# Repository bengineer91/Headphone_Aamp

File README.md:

Opamp based headphone amplifier. 

**Digital Side**

Momentary push button feeds a schmitt trigger and D flip flop to turn the board on and off. A USB-C connector with 5.1k resistors on the CC pins sets it up for 5V 3A max - this is mainly because I couldn't find a sufficiently simple USB-C PD Sink IC that I liked. Even the simple ones seemed overly complex so my conclusion is I'm not the target audience of where the industry is headed.

**Analog Side**

Isolated DC/DC converter takes 5V in and spits out +/-12V. This then feeds through an LDO to regulate the split rails at roughly +/-10V. Audio path is a 10k potentiometer, OPA1656 provides high and low pass filtering along with gain, then parallel stages of OPA1678 provide the output stage.

Sound quality is excellent although I already have a list of issues and improvements for next time. [Fixed] indicates the files uploaded here have this incorporated. I don't have a scope to make any measurements - only thing I checked was voltage rails and DC offset with my multimeter.

1. [Fixed] Connect LDO enable to VIN. (I had to make a daughterboard on the revision I built).
2. Anti-pop circuit on output.
3. [Fixed] Add cap (C35) so the on/off circuit defaults to off at power application.
4. Add switchable dummy load for testing before connecting headphones.
5. Trimpot for LED brightness.
6. Adjustable gain

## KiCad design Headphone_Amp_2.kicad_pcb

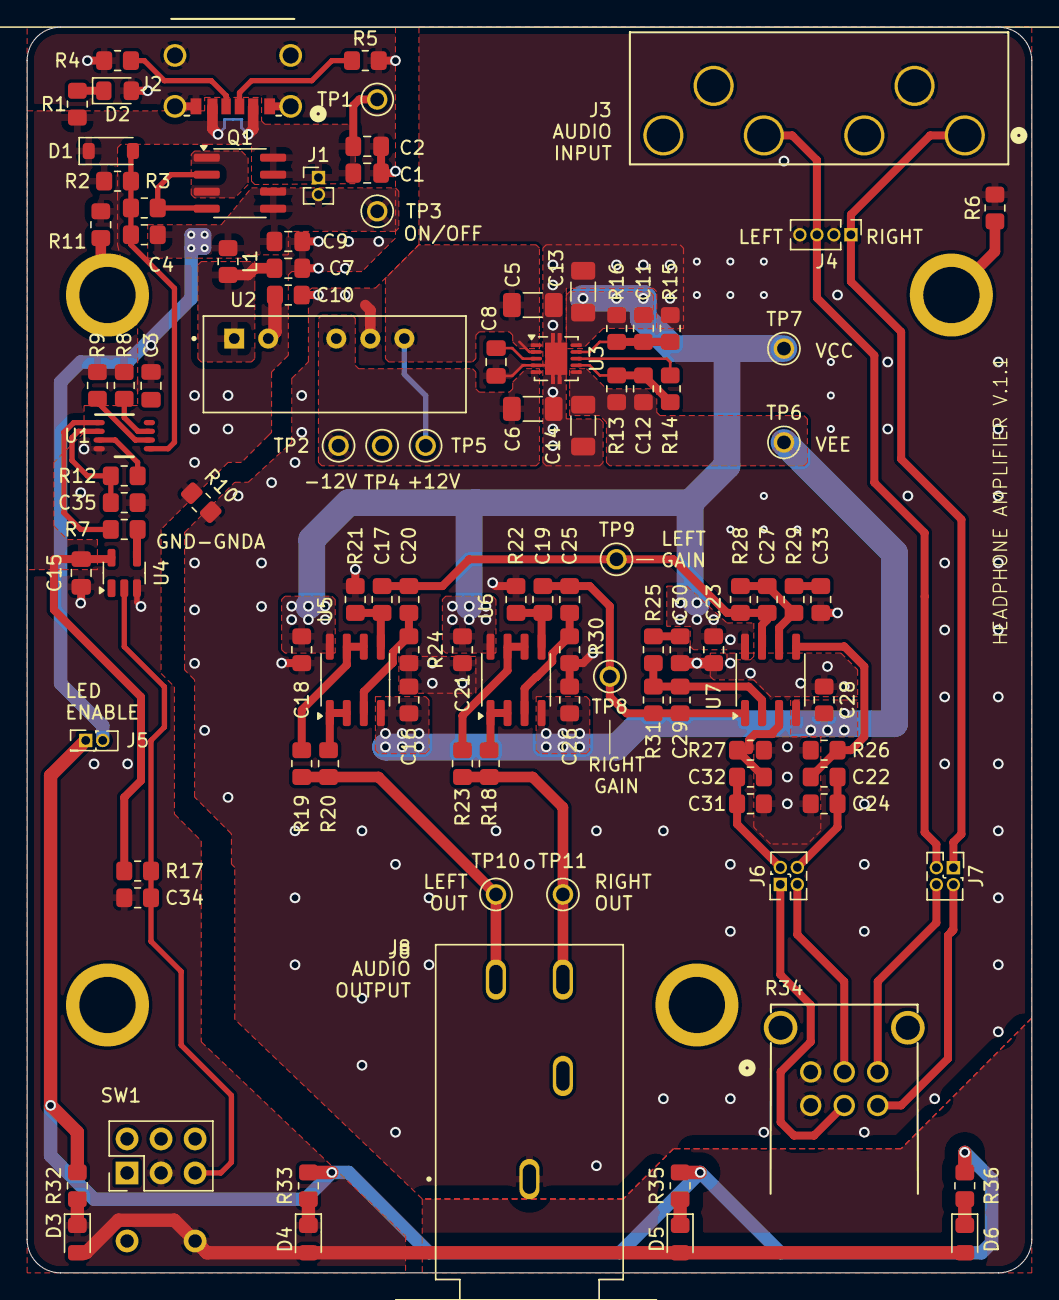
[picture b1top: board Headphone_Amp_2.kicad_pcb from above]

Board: 2 copper layers, 75.0 x 93.0 mm, 111 parts (1 on the bottom side), 59 nets.

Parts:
C1, C8: 0.01u; C_0805_2012Metric_Pad1.18x1.45mm_HandSolder
C2, C7, C9: 4.7u; C_0805_2012Metric_Pad1.18x1.45mm_HandSolder
C3, C15: 0.1u; C_0805_2012Metric_Pad1.18x1.45mm_HandSolder
C4, C34: 1000p; C_0805_2012Metric_HandSolder
C5, C6, C13, C14: 10u; C_1206_3216Metric_Pad1.33x1.80mm_HandSolder
C10: 1n; C_0805_2012Metric_HandSolder
C11, C12: 10n; C_0805_2012Metric_HandSolder
C16, C18, C21, C23, C26, C28: 100n; C_0805_2012Metric_HandSolder
C17, C19, C20, C22, C25, C30, C32, C33: 1u; C_0805_2012Metric_HandSolder
C24, C27, C29, C31: 68p; C_0805_2012Metric_HandSolder
C35: 22p; C_0805_2012Metric_HandSolder
D1: MMSZ5238BT1G; D_SOD-123
D2, D3, D4, D5, D6: LED; LED_0805_2012Metric_Pad1.15x1.40mm_HandSolder
H1, H2, H3, H4: MountingHole; Keystone_M3_Standoff
J1: Conn_02x01; PinHeader_1x02_P1.27mm_Vertical
J2: USB4125-GF-A-0190; CONN6_125-GF-A-0190_GCT
J3: PJRAN2X1U01AUX; CONN6_984x394_SWC_BS
J4: Conn_01x04; PinHeader_1x04_P1.27mm_Vertical
J5: Conn_02x01; PinHeader_2x01_P1.27mm_Vertical
J6, J7: Conn_02x02_Odd_Even; PinHeader_2x02_P1.27mm_Vertical
J8: SJ-63063B; CUI_SJ-63063B
L1: 6.8u; R_0805_2012Metric_HandSolder
Q1: IRF7324; SOIC-8_3.9x4.9mm_P1.27mm
R1, R32, R33, R35, R36: 150; R_0805_2012Metric_HandSolder
R2, R17: 10K; R_0805_2012Metric_HandSolder
R3, R7: 47; R_0805_2012Metric_HandSolder
R4, R5: 5.1K; R_0805_2012Metric_HandSolder
R6, R8, R9, R10, R11: 0; R_0805_2012Metric_HandSolder
R12: 330; R_0805_2012Metric_HandSolder
R13: 84.5k; R_0805_2012Metric_HandSolder
R14, R15, R21, R22, R24, R25, R26, R27, R28, R29, R30, R31: 10k; R_0805_2012Metric_HandSolder
R16: 75k; R_0805_2012Metric_HandSolder
R18, R19, R20, R23: 1; R_0805_2012Metric_HandSolder
R34: RK09L12B0A4S; RK09L12B0A4S_AAL
SW1: BB15AH-FA; BB16AH
TP1, TP2, TP3, TP4, TP5, TP6, TP7, TP8, TP9, TP10, TP11: 5020; KEYSTONE_5020
U1: SN74LVC1G74DCTR; DCT0008A_L
U2: PCN2-S5-D12-S; CONV_PCN2-S5-D12-S
U3: TPS7A39; Texas_S-PVSON-N10
U4: 74LVC1G17; SOT-23-5
U5, U6: OPA1678; SOIC-8_3.9x4.9mm_P1.27mm
U7: OPA1656ID; SOIC-8_3.9x4.9mm_P1.27mm
U8: TVS2200DRV; WSON-6-1EP_2x2mm_P0.65mm_EP1x1.6mm

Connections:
/USBC Input/USBC_CC1: J2.A5 (CC1), R5.1
/USBC Input/USBC_CC2: J2.B5 (CC2), R4.1
GND: C1.2, C2.2, C3.2, C7.2, C9.2, C10.1, C15.2, C34.2, C35.2, D2.2 (A), D3.1 (K), D4.1 (K), D5.1 (K), D6.1 (K), J2.7 (SHELL), J2.8 (SHELL), J2.9 (SHELL), J2.10 (SHELL), J2.A12 (GND), J2.B12 (GND), R4.2, R5.2, R10.2, R11.1, SW1.5 (B), U1.4 (GND), U2.2 (-VIN), U4.3 (GND), U8.1 (GND), U8.2 (GND), U8.3 (GND), U8.7 (GND)
GNDA: C5.2, C6.1, C8.2, C10.2, C13.2, C14.1, C16.1, C18.2, C21.2, C23.2, C24.2, C26.1, C28.1, C30.1, C31.2, C33.1, J3.1, J3.4, J4.2, J4.4, J8.1, R6.2, R10.1, R15.1, R21.1, R22.1, R24.1, R26.1, R27.1, R30.1, R34.1, R34.4, TP4.TP, U2.5 (COMMON), U3.4 (GND), U3.11 (GND)
Left_In: J3.5, J4.3, J7.3
unnamed: C17.1, C20.1, C27.1, R28.2, TP9.TP, U7.7
unnamed: C19.1, C25.1, C29.1, R31.2, TP8.TP, U7.1
unnamed: C30.2, R25.1
unnamed: C33.2, R29.1
unnamed: C4.2, D1.2 (A), R2.2, R3.1, U1.5 (Q)
unnamed: D2.1 (K), R1.2
unnamed: D3.2 (A), R32.2
unnamed: D4.2 (A), R33.2
unnamed: D5.2 (A), R35.2
unnamed: D6.2 (A), R36.2
unnamed: H1.1, R11.2
unnamed: H2.1, R6.1
unnamed: J5.1, R32.1, R33.1, R35.1, R36.1
unnamed: J6.1, R34.2
unnamed: C31.1, C32.1, J6.2
unnamed: J6.3, R34.5
unnamed: C22.1, C24.1, J6.4
unnamed: J7.2, R34.3
unnamed: J7.4, R34.6
unnamed: J8.2, R18.1, R23.1, TP11.TP
unnamed: J8.3, R19.1, R20.1, TP10.TP
unnamed: Q1.2 (G1), Q1.4 (G2), R3.2
unnamed: Q1.1 (S1), Q1.3 (S2)
unnamed: R7.2, U4.4
unnamed: C34.1, R17.2, SW1.6 (C), U4.2
unnamed: R7.1, U1.1 (CLK)
unnamed: R9.2, U1.6 (CLR_N)
unnamed: C35.1, R12.1, U1.2 (D)
unnamed: R8.2, U1.7 (PRE_N)
unnamed: R12.2, U1.3 (Q_N)
unnamed: C7.1, L1.2, U2.1 (+VIN)
unnamed: C5.1, TP5.TP, U2.6 (+VOUT), U3.1 (INP), U3.2 (EN)
unnamed: C6.2, TP2.TP, U2.4 (-VOUT), U3.5 (INN)
unnamed: R14.2, U3.8 (BUF)
unnamed: C12.1, R13.2, R14.1, U3.7 (FBN)
unnamed: C11.2, R15.2, R16.1, U3.9 (FBP)
unnamed: C8.1, U3.3 (NR/SS)
unnamed: C20.2, R24.2, U5.3 (+)
unnamed: R20.2, U5.1, U5.2 (-)
unnamed: C17.2, R21.2, U5.5 (+)
unnamed: R19.2, U5.6 (-), U5.7
unnamed: C25.2, R30.2, U6.3 (+)
unnamed: R18.2, U6.1, U6.2 (-)
unnamed: C19.2, R22.2, U6.5 (+)
unnamed: R23.2, U6.6 (-), U6.7
unnamed: C32.2, R27.2, U7.3 (+)
unnamed: C29.2, R25.2, R31.1, U7.2 (-)
unnamed: C22.2, R26.2, U7.5 (+)
unnamed: C27.2, R28.1, R29.2, U7.6 (-)
Right_In: J3.2, J4.1, J7.1
USBC_ON/OFF: C4.1, C9.1, J1.2, J5.2, L1.1, Q1.5 (D2), Q1.6 (D2), TP3.TP
USBC_VBUS: C1.1, C2.1, C3.1, C15.1, D1.1 (K), J1.1, J2.A9 (VBUS), J2.B9 (VBUS), Q1.7 (D1), Q1.8 (D1), R1.1, R2.1, R8.1, R9.1, R17.1, TP1.TP, U1.8 (VCC), U4.5 (VCC), U8.4 (IN), U8.5 (IN), U8.6 (IN)
VCC: C11.1, C13.1, C18.1, C21.1, C23.1, R16.2, TP7.TP, U3.10 (OUTP), U5.8 (V+), U6.8 (V+), U7.8 (V+)
VEE: C12.2, C14.2, C16.2, C26.2, C28.2, R13.1, TP6.TP, U3.6 (OUTN), U5.4 (V-), U6.4 (V-), U7.4 (V-)
